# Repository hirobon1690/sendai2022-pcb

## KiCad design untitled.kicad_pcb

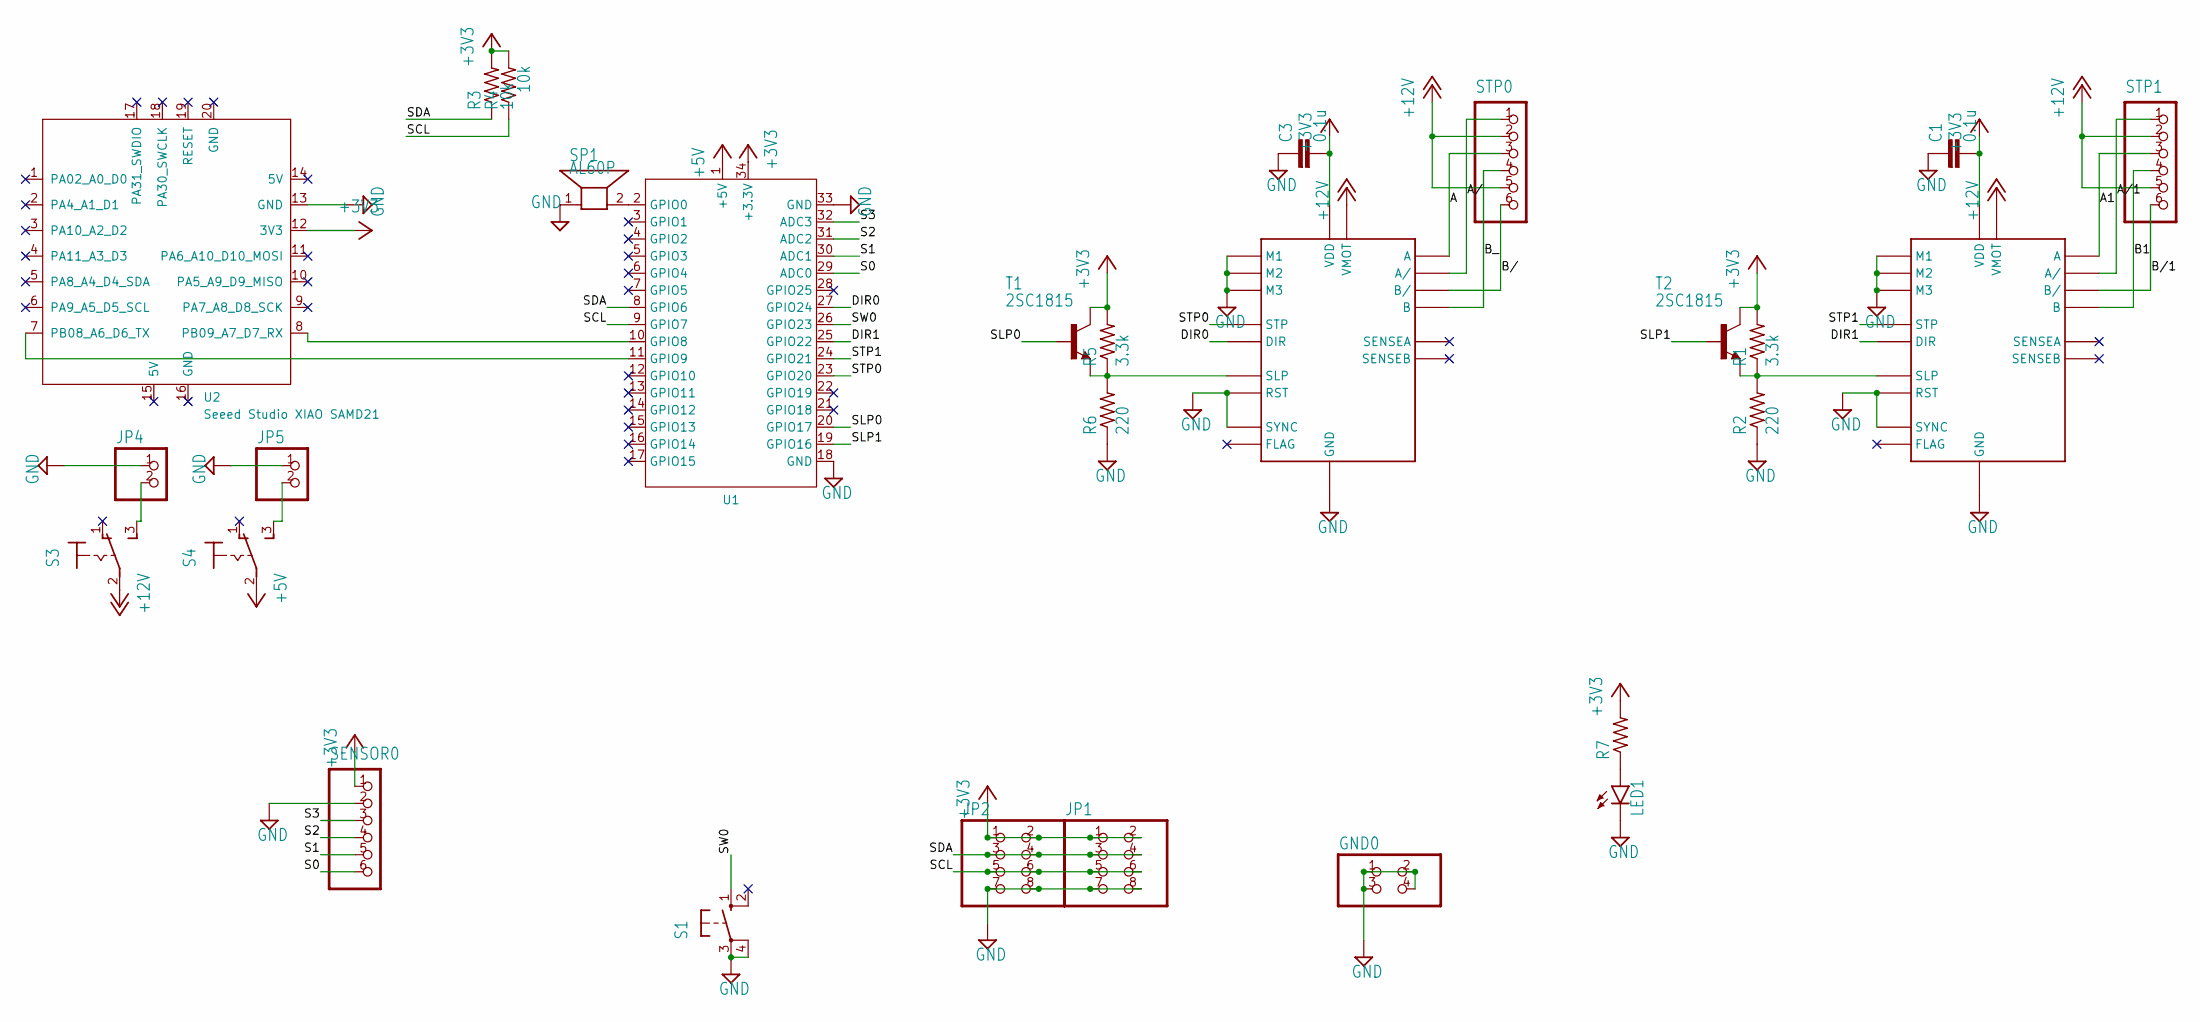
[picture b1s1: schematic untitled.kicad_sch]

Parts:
C1, C3: 0.1u; C025-024X044
GND0: PINHD-2X2; 2X02
JP1, JP2: PINHD-2X4; 2X04
JP4, JP5: PINHD-1X2/90; 1X02_90
LED1: LED3MM
R1, R5: 3.3k; 0204_5
R2, R6: 220; 0204_5
R3, R4: 10k; 0204_5
R7: R-US_0204/5; 0204_5
S1: 10-XX; B3F-10XX
S3, S4: TOGGLE
SENSOR0: XH-6
SP1: AL60P
STP0, STP1: XH-6
T1, T2: 2SC1815; TO92-ECB
U1: AE-RP2040
U2: Seeed Studio XIAO SAMD21; XIAO-ESP32C3-14P-2.54-21X17.8MM
U$2, U$3: SLA7073MPRT

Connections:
+3V3: C1.2, C3.2, JP1.1, JP1.2, JP2.1, JP2.2, R1.2, R3.2, R4.2, R5.2, R7.2, SENSOR0.1, T1.C, T2.C, U1.34 (+3.3V), U2.12 (3V3), U$2.VDD, U$3.VDD
+5V: S4.2, U1.1 (+5V)
+12V: S3.2, STP0.2, STP0.5, STP1.2, STP1.5, U$2.VBB (VMOT), U$3.VBB (VMOT)
/A: STP0.3, U$2.OUTA1 (A), U$2.OUTA2 (A)
/A1: STP1.3, U$3.OUTA1 (A), U$3.OUTA2 (A)
/A/: STP0.1, U$2.OUTA/1 (A/), U$2.OUTA/2 (A/)
/A/1: STP1.1, U$3.OUTA/1 (A/), U$3.OUTA/2 (A/)
/B1: STP1.4, U$3.OUTB1 (B), U$3.OUTB2 (B)
/B_: STP0.4, U$2.OUTB1 (B), U$2.OUTB2 (B)
/B/: STP0.6, U$2.OUTB/1 (B/), U$2.OUTB/2 (B/)
/B/1: STP1.6, U$3.OUTB/1 (B/), U$3.OUTB/2 (B/)
/DIR0: U1.27 (GPIO24), U$2.DIR
/DIR1: U1.25 (GPIO22), U$3.DIR
/S0: SENSOR0.6, U1.29 (ADC0)
/S1: SENSOR0.5, U1.30 (ADC1)
/S2: SENSOR0.4, U1.31 (ADC2)
/S3: SENSOR0.3, U1.32 (ADC3)
/SCL: JP1.5, JP1.6, JP2.5, JP2.6, R4.1, U1.9 (GPIO7)
/SDA: JP1.3, JP1.4, JP2.3, JP2.4, R3.1, U1.8 (GPIO6)
/SLP0: T1.B, U1.20 (GPIO17)
/SLP1: T2.B, U1.19 (GPIO16)
/STP0: U1.23 (GPIO20), U$2.CLK (STP)
/STP1: U1.24 (GPIO21), U$3.CLK (STP)
/SW0: S1.1 (S), U1.26 (GPIO23)
GND: C1.1, C3.1, GND0.1, GND0.2, GND0.3, GND0.4, JP1.7, JP1.8, JP2.7, JP2.8, JP4.1, JP5.1, LED1.K (C), R2.1, R6.1, S1.3, S1.4 (P1), SENSOR0.2, SP1.1, U1.18 (GND), U1.33 (GND), U2.13 (GND), U$2.GND, U$2.M1, U$2.M2, U$2.M3, U$2.RST, U$2.SYNC, U$3.GND, U$3.M1, U$3.M2, U$3.M3, U$3.RST, U$3.SYNC
unnamed: LED1.A, R7.1
unnamed: R1.1, R2.2, T2.E, U$3.SLP
unnamed: R5.1, R6.2, T1.E, U$2.SLP
unnamed: JP4.2, S3.3 (S)
unnamed: JP5.2, S4.3 (S)
unnamed: SP1.2, U1.2 (GPIO0)
unnamed: U1.10 (GPIO8), U2.8 (PB09_A7_D7_RX)
unnamed: U1.11 (GPIO9), U2.7 (PB08_A6_D6_TX)

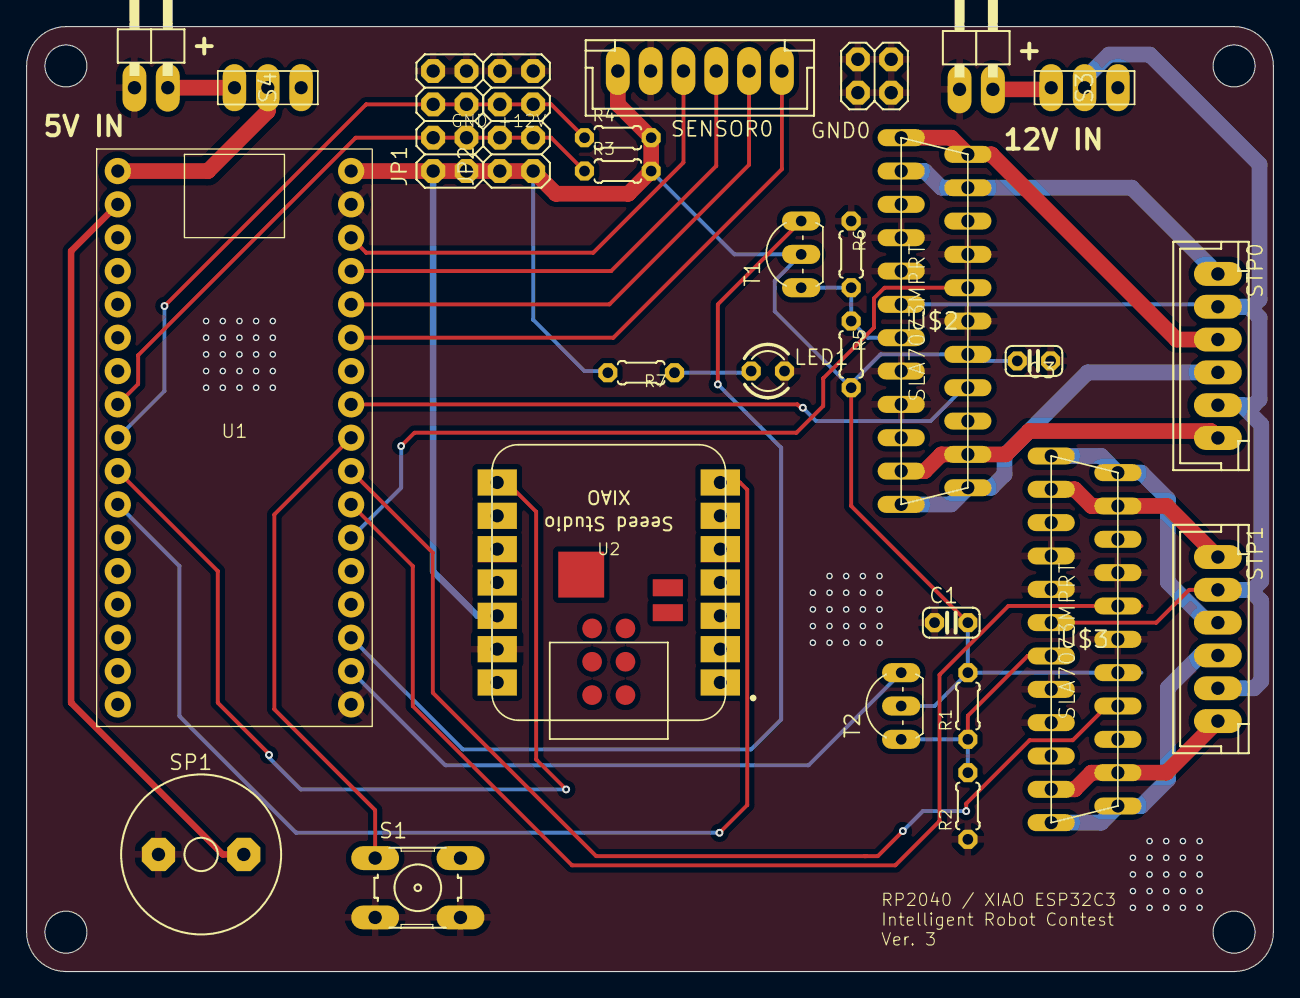
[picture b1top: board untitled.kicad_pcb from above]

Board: 2 copper layers, 95.0 x 72.0 mm, 28 parts (0 on the bottom side), 33 nets.

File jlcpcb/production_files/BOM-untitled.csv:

Comment,Designator,Footprint,LCSC
Seeed Studio XIAO SAMD21,U2,XIAO-ESP32C3-14P-2.54-21X17.8MM,
~,U1,AE-RP2040,
2SC1815,T2,TO92-ECB,
2SC1815,T1,TO92-ECB,
XH-6,STP1,XH-6,
XH-6,STP0,XH-6,
AL60P,SP1,AL60P,
XH-6,SENSOR0,XH-6,
TOGGLE,S4,TOGGLE,
TOGGLE,S3,TOGGLE,
10-XX,S1,B3F-10XX,
R-US_0204/5,R7,0204_5,
220,R6,0204_5,
3.3k,R5,0204_5,
10k,R4,0204_5,
10k,R3,0204_5,
220,R2,0204_5,
3.3k,R1,0204_5,
LED3MM,LED1,LED3MM,
PINHD-1X2/90,JP5,1X02_90,
PINHD-1X2/90,JP4,1X02_90,
PINHD-2X4,JP2,2X04,
PINHD-2X4,JP1,2X04,
PINHD-2X2,GND0,2X02,
0.1u,C3,C025-024X044,
0.1u,C1,C025-024X044,
